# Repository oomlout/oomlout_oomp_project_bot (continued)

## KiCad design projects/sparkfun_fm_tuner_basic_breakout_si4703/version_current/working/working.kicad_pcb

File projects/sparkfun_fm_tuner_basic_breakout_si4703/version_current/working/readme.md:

# FM_Tuner_Basic_Breakout-Si4703 by sparkfun  
This is a harvested standardized copy of a project from github.  
The original project can be found at:  
https://github.com/sparkfun/FM_Tuner_Basic_Breakout-Si4703  
Please consult that link for additional, details, files, and license information.  
Note: It was auto harvested and if the original repo had more than one board file or anything out of the ordinary the files here are likely not representative.

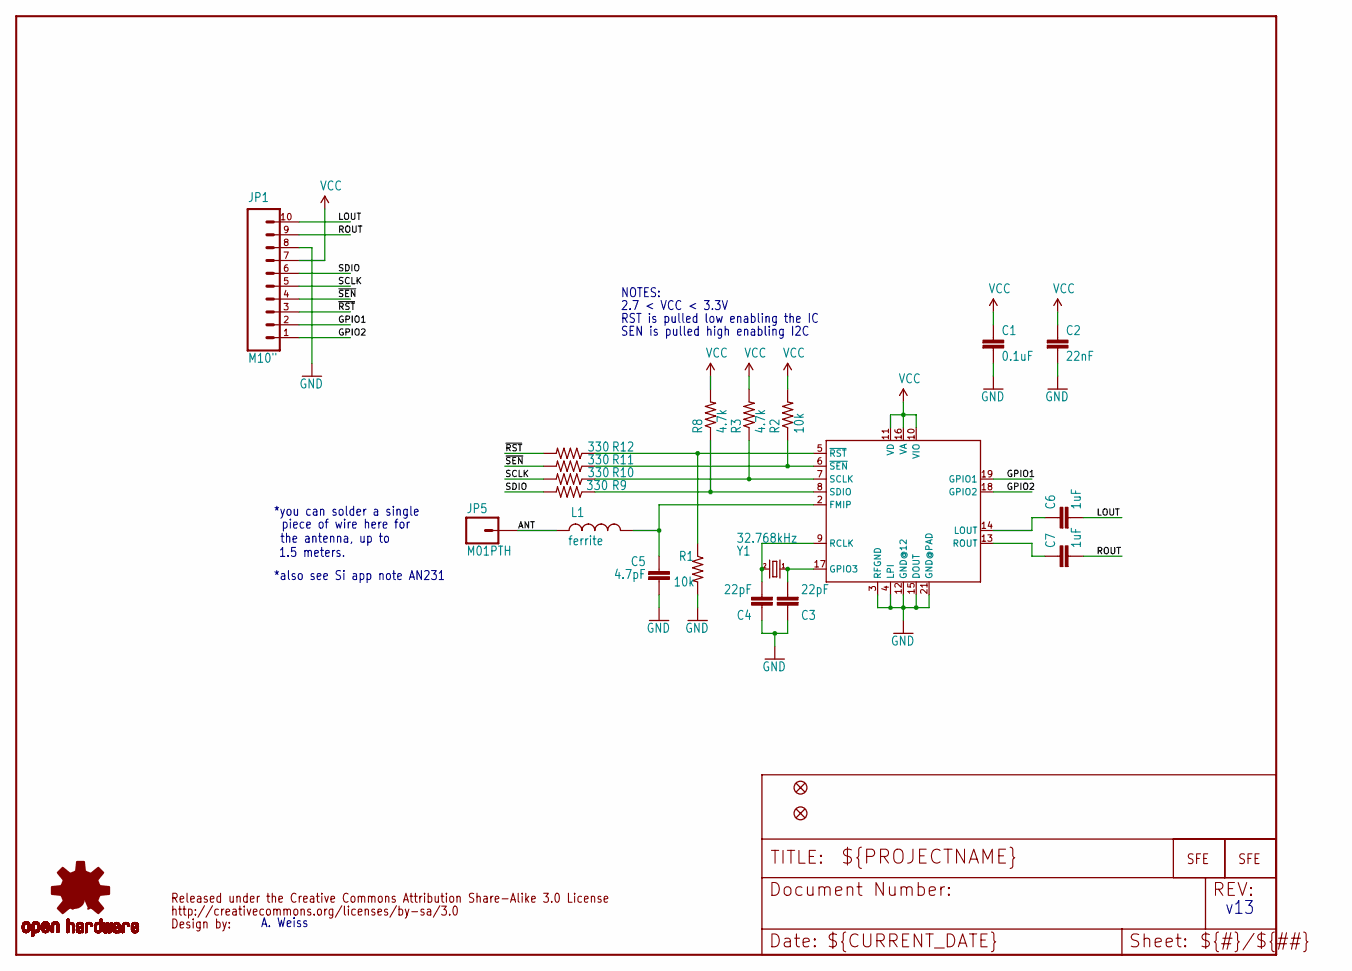
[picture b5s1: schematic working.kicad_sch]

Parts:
C1: 0.1uF; 0402-CAP
C2: 22nF; 0402-CAP
C3, C4: 22pF; 0402-CAP
C5: 4.7pF; 0402-CAP
C6, C7: 1uF; 0402-CAP
JP1: M10"; 1X10
JP2: LOGO-SFENW2; SFE-NEW-WEB
JP3: LOGO-SFESK; SFE-LOGO-FLAME
JP4, JP6: FIDUCIALUFIDUCIAL; MICRO-FIDUCIAL
JP5: M01PTH; 1X01
L1: ferrite; C0402
R1, R2: 10k; 0402-RES
R3, R8: 4.7k; 0402-RES
R9, R10, R11, R12: 330; 0402-RES
U1: SPARKFUN_SI470X
U$1: CREATIVE_COMMONS
U$3: OSHW-LOGOS; OSHW-LOGO-S
Y1: 32.768kHz; CRYSTAL-32KHZ-SMD

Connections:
3.3V: C1.1, C2.1, JP1.7, R2.2, R3.2, R8.2, U1.10 (VIO), U1.11 (VD), U1.16 (VA)
ANT: JP5.1, L1.1
GND: C1.2, C2.2, C3.1, C4.1, C5.2, JP1.8, R1.2, U1.3 (RFGND), U1.4 (LPI), U1.12 (GND@12), U1.15 (DOUT), U1.21 (GND@PAD)
GPIO1: JP1.2, U1.19 (GPIO1)
GPIO2: JP1.1, U1.18 (GPIO2)
LOUT: C6.2, JP1.10
unnamed: C4.2, U1.9 (RCLK), Y1.X2 (2)
unnamed: C3.2, U1.17 (GPIO3), Y1.X1 (1)
unnamed: C5.1, L1.2, U1.2 (FMIP)
unnamed: C6.1, U1.14 (LOUT)
unnamed: C7.1, U1.13 (ROUT)
ROUT: C7.2, JP1.9
SCLK: JP1.5, R10.2
SCLK-L: R3.1, R10.1, U1.7 (SCLK)
SDIO: JP1.6, R9.2
SDIO-L: R8.1, R9.1, U1.8 (SDIO)
~RST-L: R1.1, R12.1, U1.5 (~RST)
~RST: JP1.3, R12.2
~SEN-L: R2.1, R11.1, U1.6 (~SEN)
~SEN: JP1.4, R11.2

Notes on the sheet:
*also see Si app note AN231
SEN is pulled high enabling I2C
*you can solder a single
v13
A. Weiss
piece of wire here for
NOTES:
1.5 meters.
RST is pulled low enabling the IC
2.7 < VCC < 3.3V
the antenna, up to

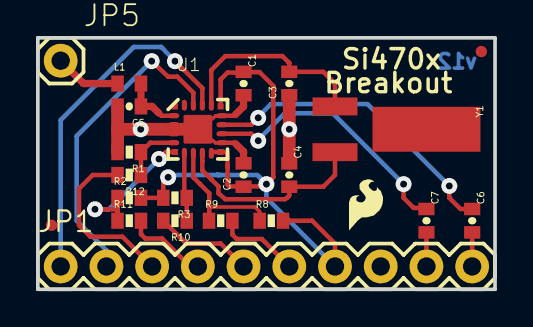
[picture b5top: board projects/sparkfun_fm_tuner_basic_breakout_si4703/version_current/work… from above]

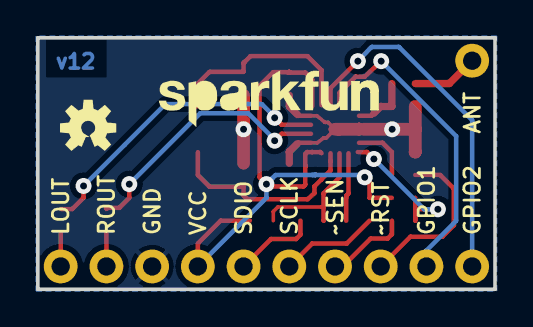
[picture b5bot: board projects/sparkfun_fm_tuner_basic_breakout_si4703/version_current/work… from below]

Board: 2 copper layers, 25.4 x 14.0 mm, 26 parts (2 on the bottom side), 20 nets.

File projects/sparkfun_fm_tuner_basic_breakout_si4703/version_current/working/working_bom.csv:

Row,Description,Part,References,Value,Footprint,Quantity Per PCB,Status,Datasheet,RESISTANCE
1,,CAP0402-CAP,C5,4.7pF,0402-CAP,1, ,,
2,,CAP0402-CAP,C3 C4,22pF,0402-CAP,2, ,,
3,,CAP0402-CAP,C2,22nF,0402-CAP,1, ,,
4,,CAP0402-CAP,C1,0.1uF,0402-CAP,1, ,,
5,,CAP0402-CAP,C6 C7,1uF,0402-CAP,2, ,,
6,,LOGO-SFENW2,JP2,LOGO-SFENW2,SFE-NEW-WEB,1, ,,
7,,LOGO-SFESK,JP3,LOGO-SFESK,SFE-LOGO-FLAME,1, ,,
8,,M01PTH,JP5,M01PTH,1X01,1, ,,
9,,M10{dblquote},JP1,M10{dblquote},1X10,1, ,,
10,,INDUCTOR0402,L1,ferrite,C0402,1, ,,75 Ohm
11,,RESISTOR0402-RES,R9 R10 R11 R12,330,0402-RES,4, ,,
12,,RESISTOR0402-RES,R3 R8,4.7k,0402-RES,2, ,,
13,,RESISTOR0402-RES,R1 R2,10k,0402-RES,2, ,,
14,,SPARKFUN_SI470X,U1,SPARKFUN_SI470X,SPARKFUN_SI470X,1, ,,
15,,CREATIVE_COMMONS,U$1,CREATIVE_COMMONS,CREATIVE_COMMONS,1, ,,
16,,OSHW-LOGOS,U$3,OSHW-LOGOS,OSHW-LOGO-S,1, ,,
17,,CRYSTAL32-SMD,Y1,32.768kHz,CRYSTAL-32KHZ-SMD,1, ,,





Project info:
Schematic:,working
Variant:,default
Revision:,
Date:,2023-08-06_12-56-02
KiCad Version:,7.0.6-7.0.6~ubuntu22.04.1
Statistics:
Component Groups:,17
Component Count:,24 (0 SMD/ 0 THT)
Fitted Components:,24 (0 SMD/ 0 THT)
Number of PCBs:,1
Total Components:,24

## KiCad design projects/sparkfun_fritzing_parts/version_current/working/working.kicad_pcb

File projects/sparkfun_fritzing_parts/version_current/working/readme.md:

# OOMP Project  
## Fritzing_Parts  by sparkfun  
  
oomp key: oomp_projects_flat_sparkfun_fritzing_parts  
(snippet of original readme)  
  
Fritzing Parts  
==============  
  
This repo houses all of the SFE Fritzing parts for use in diagrams in tutorials. If you create a new part in Fritzing that correlates to an SFE part, please add it here so others may use it and to avoid duplication. Make sure to also check Fritzing software for additional boards.   
  
Repository Contents  
-------------------  
  
* **/kits** - Fritzing circuits (**&-42;.fzz**) and images (**&-42;.png**)from a few of our Inventor's Kits  
* **/parts** - Common Fritzing parts and vector (**&-42;.svg**) files of individual components on SparkFun boards  
* **/products** - Fritzing boards (**&-42;.fzpz** and some **&-42;.fzz**)  
* **/templates** - SparkFun T5403 Barometer Breakout vector (**&-42;.svg**) templates used in the SparkFun tutorial to [Make Your Own Fritzing Part]((https://learn.sparkfun.com/tutorials/make-your-own-fritzing-parts) )  
  
Documentation  
-------------  
* [Make Your Own Fritzing Parts](https://learn.sparkfun.com/tutorials/make-your-own-fritzing-parts)   
  
Contributing/Adding Fritzing Parts  
---------------------------------  
  
Please check out the Fritzing tutorial [here](https://github.com/fritzing/fritzing-parts/blob/master/CONTRIBUTING.md) for more information.   
  
  full source readme at [readme_src.md](readme_src.md)  
  
source repo at: [https://github.com/sparkfun/Fritzing_Parts](https://github.com/sparkfun/Fritzing_Parts)  
## Board  

## Schematic  

[schematic pdf](working_schematic.pdf)  
## Images

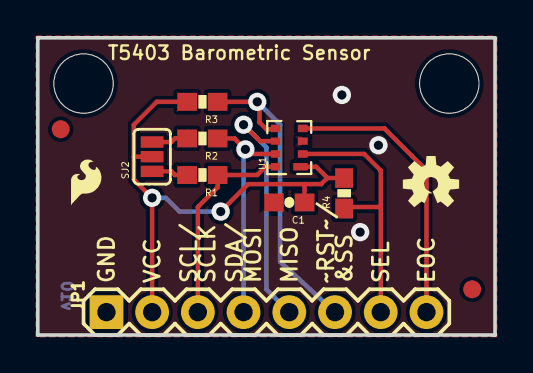
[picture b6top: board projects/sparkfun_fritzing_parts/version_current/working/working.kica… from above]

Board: 2 copper layers, 25.4 x 16.5 mm, 16 parts (1 on the bottom side), 10 nets.

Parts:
C1: .1uF; 0603-CAP
FID1, FID2: FIDUCIAL1X2; FIDUCIAL-1X2
FRAME1: FRAME-LETTER; CREATIVE_COMMONS
JP1: 1X08
LOGO1: LOGO-SFENEW; SFE-NEW-WEBLOGO
LOGO2: OSHW-LOGOS; OSHW-LOGO-S
LOGO3: SFE_LOGO_FLAME.1_INCH; SFE_LOGO_FLAME_.1
R1, R2: 4.7k; 0603-RES
R3, R4: 10k; 0603-RES
SJ2: SJ_3_PASTE1&2&3
STANDOFF1, STANDOFF2: STAND-OFF
U1: T5400

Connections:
EOC: JP1.8, U1.4
GND: C1.2, JP1.1, U1.3
MISO: JP1.5, U1.6
unnamed: R2.2, SJ2.3
unnamed: R1.2, SJ2.1
SCL/SCLK: JP1.3, R1.1, U1.8
SDA/MOSI: JP1.4, R2.1, U1.7
SEL: JP1.7, R4.1, U1.2
VCC: C1.1, JP1.2, R3.2, R4.2, SJ2.2, U1.1
~RST/&SS: JP1.6, R3.1, U1.5

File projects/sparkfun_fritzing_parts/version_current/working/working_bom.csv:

"Id";"Designator";"Footprint";"Quantity";"Designation";"Supplier and ref";
1;"LOGO2";"OSHW-LOGO-S";1;"OSHW-LOGOS";;;
2;"STANDOFF1,STANDOFF2";"STAND-OFF";2;"STAND-OFF";;;
3;"R2,R1";"0603-RES";2;"4.7k";;;
4;"FRAME1";"CREATIVE_COMMONS";1;"FRAME-LETTER";;;
5;"SJ2";"SJ_3_PASTE1&2&3";1;"";;;
6;"LOGO3";"SFE_LOGO_FLAME_.1";1;"SFE_LOGO_FLAME.1_INCH";;;
7;"R3,R4";"0603-RES";2;"10k";;;
8;"FID1,FID2";"FIDUCIAL-1X2";2;"FIDUCIAL1X2";;;
9;"JP1";"1X08";1;"";;;
10;"C1";"0603-CAP";1;".1uF";;;
11;"U1";"T5400";1;"T5400";;;
12;"LOGO1";"SFE-NEW-WEBLOGO";1;"LOGO-SFENEW";;;

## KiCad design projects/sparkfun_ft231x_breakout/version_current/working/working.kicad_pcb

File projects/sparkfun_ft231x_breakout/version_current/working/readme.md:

# OOMP Project  
## FT231X_Breakout  by sparkfun  
  
oomp key: oomp_projects_flat_sparkfun_ft231x_breakout  
(snippet of original readme)  
  
FT231X Breakout  
========================  
  
[    
*FT231X Breakout (BOB-11736)*](https://www.sparkfun.com/products/11736)  
  
This is a simple breakout board for the FTDI FT231X. A **USB to serial UART** interface with full modem control. The board has a micro USB connector, and other support circuitry to get the IC quickly up-and-running.  
  
Repository Contents  
-------------------  
  
* **/hardware** - PCB design files (created with Eagle 6.1.0)  
* **/Production Files** - Test bed files and production panel files  
  
License Information  
-------------------  
  
All contents of this repository are released under [Creative Commons Share-alike 3.0](http://creativecommons.org/licenses/by-sa/3.0/).  
  
Author  
------  
  
Jim Lindblom, [SparkFun Electronics](https://www.sparkfun.com)  
  
  full source readme at [readme_src.md](readme_src.md)  
  
source repo at: [https://github.com/sparkfun/FT231X_Breakout](https://github.com/sparkfun/FT231X_Breakout)  
## Board  

## Schematic  

[schematic pdf](working_schematic.pdf)  
## Images

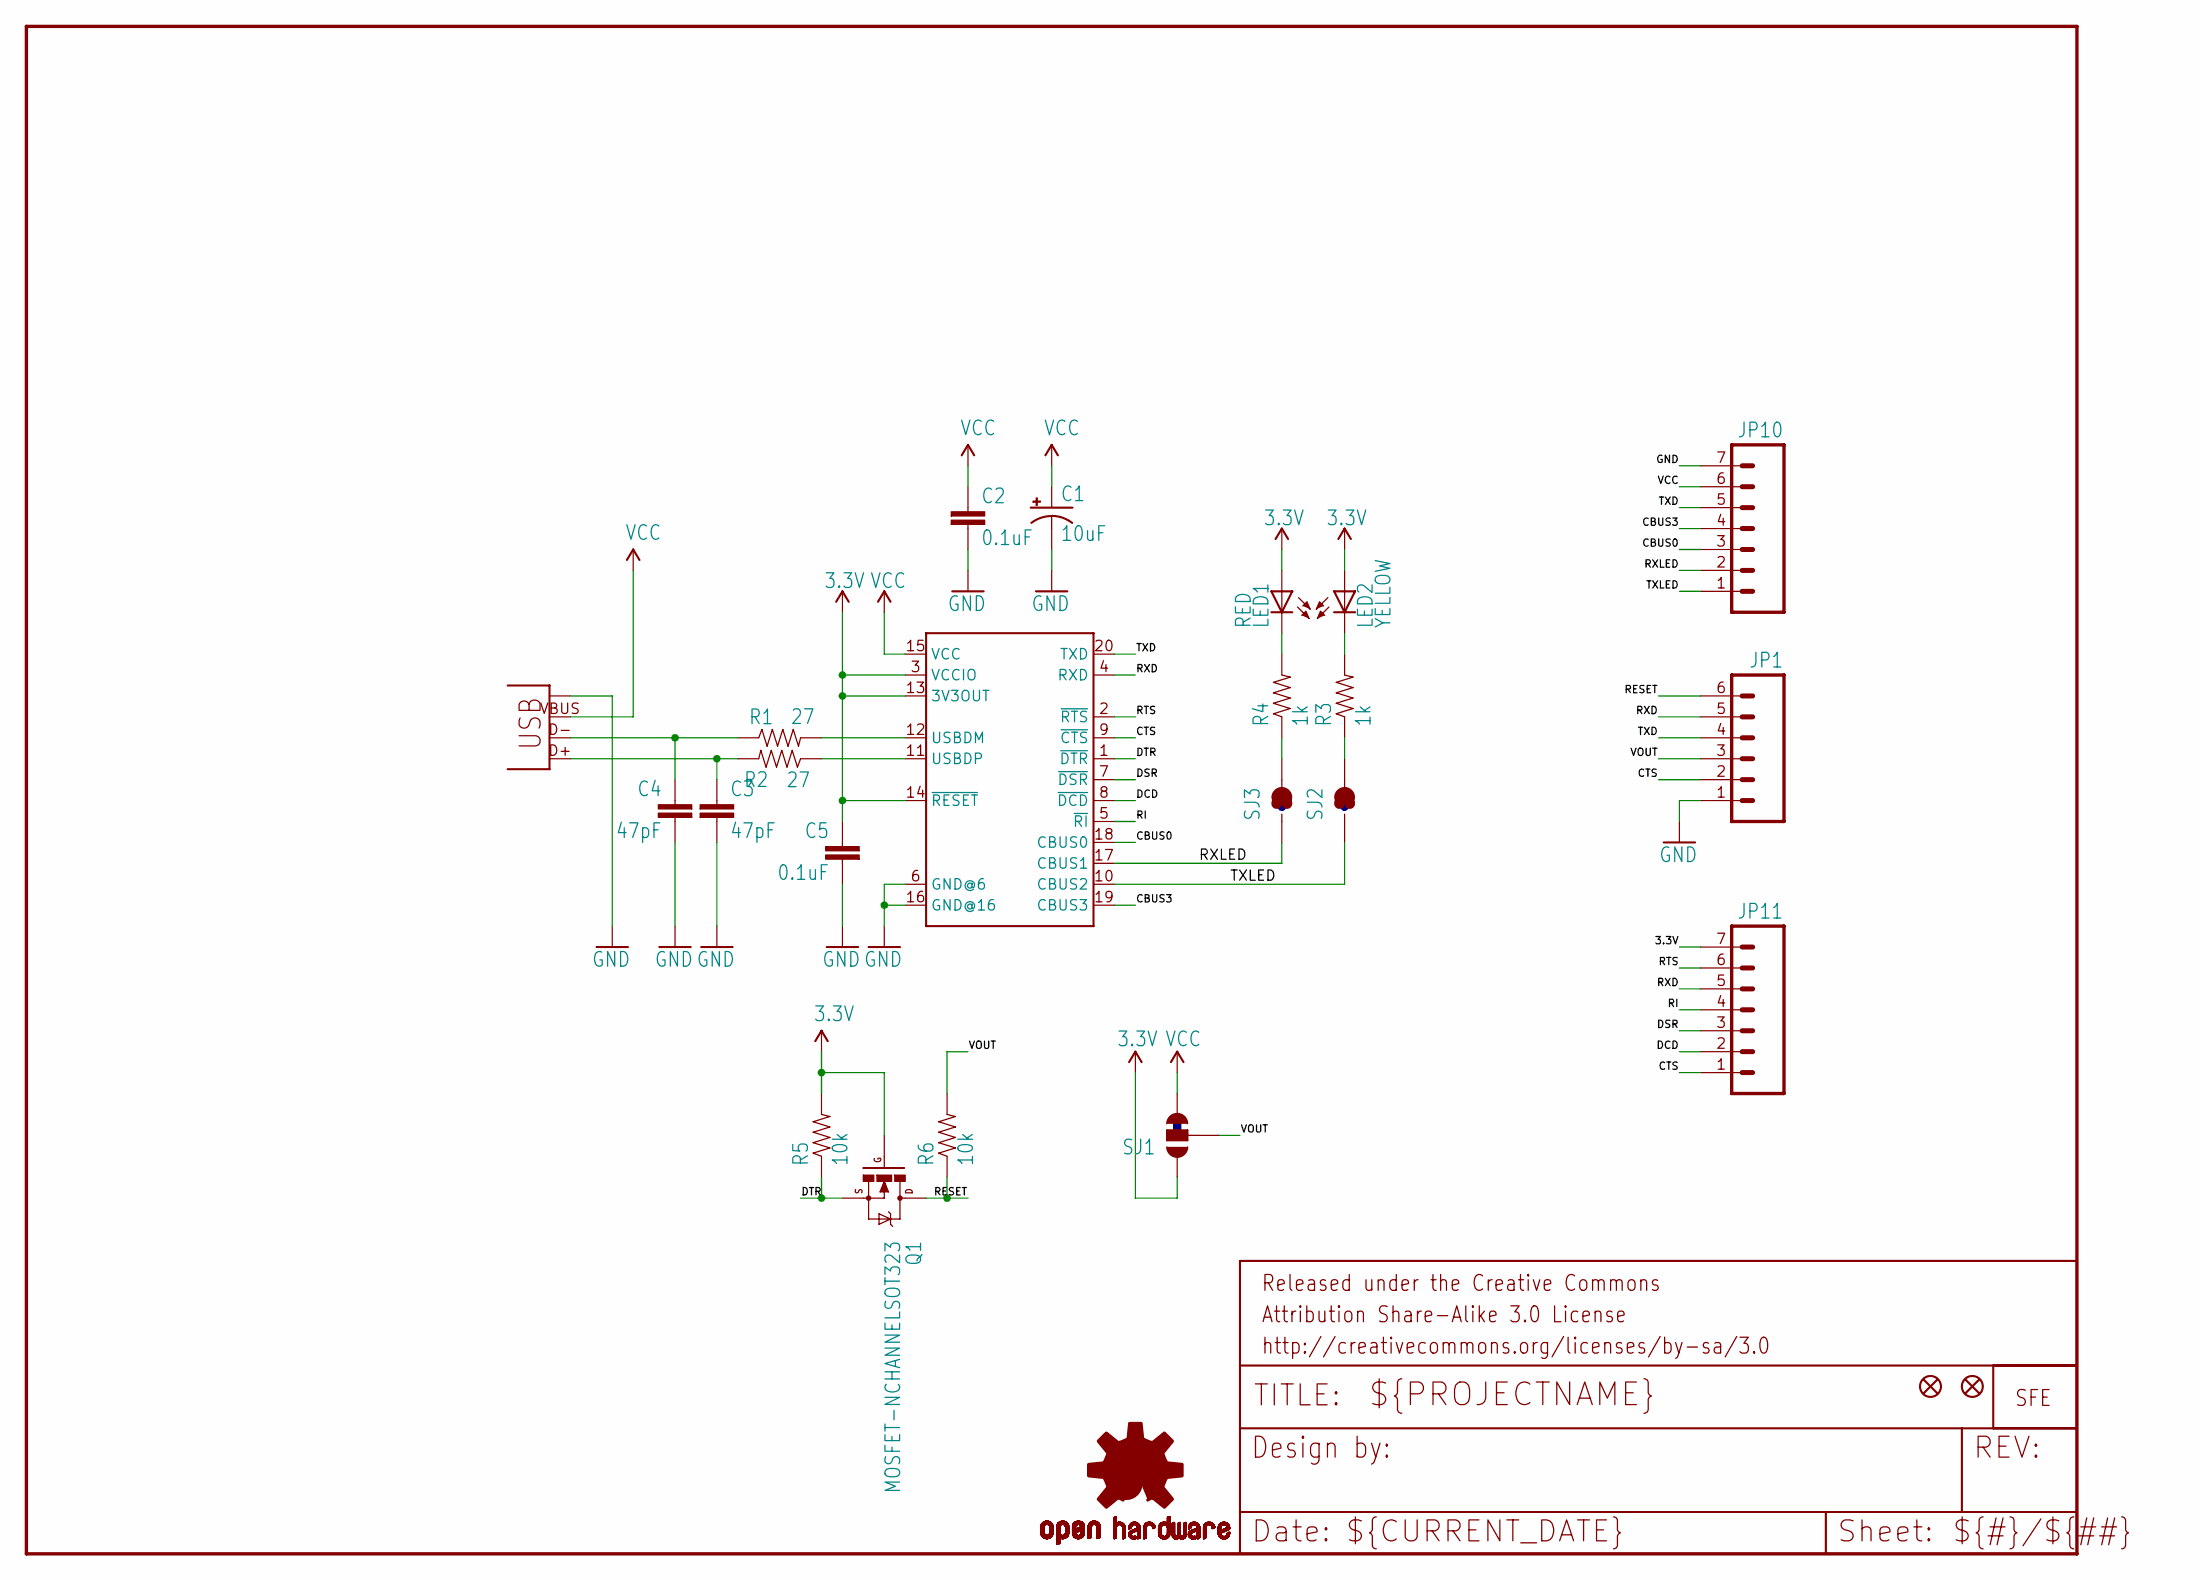
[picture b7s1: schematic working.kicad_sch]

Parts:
C1: 10uF; EIA3216
C2, C5: 0.1uF; 0402-CAP
C3, C4: 47pF; 0402-CAP
FRAME1: FRAME-LETTER; CREATIVE_COMMONS
JP1: M06SIP-NS; 1X06_NS
JP2: LOGO-SFENW2; SFE-NEW-WEB
JP3, JP4: FIDUCIALUFIDUCIAL; MICRO-FIDUCIAL
JP10, JP11: M07NS; 1X07_NS
LED1: RED; LED-0603
LED2: YELLOW; LED-0603
Q1: MOSFET-NCHANNELSOT323; SOT323
R1, R2: 27; 0402-RES
R3, R4: 1k; 0402-RES
R5, R6: 10k; 0402-RES
SJ1: SOLDERJUMPER_2WAYS; SJ_3
SJ2, SJ3: SOLDERJUMPERTRACE; SJ_2S-TRACE
U1: FT231XS; SSOP20_L
U$1: OSHW-LOGOS; OSHW-LOGO-S
X1: USB-MICROB

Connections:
3.3V: C5.1, JP11.7, LED1.A, LED2.A, Q1.1 (G), R5.2, SJ1.1, U1.3 (VCCIO), U1.13 (3V3OUT), U1.14 (~RESET)
CBUS0: JP10.3, U1.18 (CBUS0)
CBUS3: JP10.4, U1.19 (CBUS3)
CTS: JP1.2, JP11.1, U1.9 (~CTS)
DCD: JP11.2, U1.8 (~DCD)
DSR: JP11.3, U1.7 (~DSR)
DTR: Q1.2 (S), R5.1, U1.1 (~DTR)
GND: C1.C (-), C2.2, C3.2, C4.2, C5.2, JP1.1, JP10.7, U1.6 (GND@6), U1.16 (GND@16), X1.GND, X1.MT1 (GND), X1.MT2 (GND)
unnamed: R1.2, U1.12 (USBDM)
unnamed: R2.1, U1.11 (USBDP)
unnamed: C3.1, R2.2, X1.D+
unnamed: C4.1, R1.1, X1.D-
unnamed: LED2.C, R3.2
unnamed: LED1.C, R4.2
unnamed: R3.1, SJ2.2
unnamed: R4.1, SJ3.2
RESET: JP1.6, Q1.3 (D), R6.1
RI: JP11.4, U1.5 (~RI)
RTS: JP11.6, U1.2 (~RTS)
RXD: JP1.5, JP11.5, U1.4 (RXD)
RXLED: JP10.2, SJ3.1, U1.17 (CBUS1)
TXD: JP1.4, JP10.5, U1.20 (TXD)
TXLED: JP10.1, SJ2.1, U1.10 (CBUS2)
VCC: C1.A (+), C2.1, JP10.6, SJ1.3, U1.15 (VCC), X1.VBUS
VOUT: JP1.3, R6.2, SJ1.2

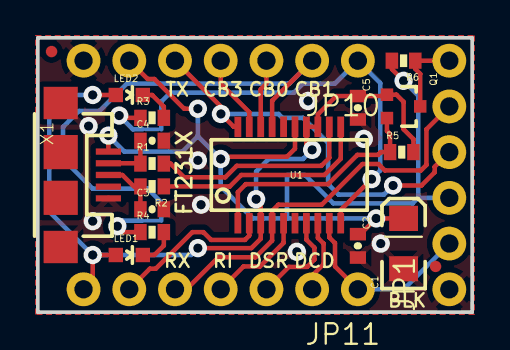
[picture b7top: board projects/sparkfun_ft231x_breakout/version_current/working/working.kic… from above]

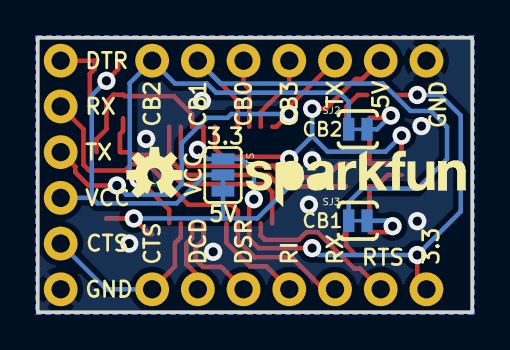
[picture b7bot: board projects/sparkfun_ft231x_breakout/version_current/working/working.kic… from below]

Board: 2 copper layers, 24.1 x 15.2 mm, 27 parts (5 on the bottom side), 25 nets.

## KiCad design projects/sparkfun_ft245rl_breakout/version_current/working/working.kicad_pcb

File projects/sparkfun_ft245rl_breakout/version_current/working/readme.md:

# OOMP Project  
## FT245RL_Breakout  by sparkfun  
  
oomp key: oomp_projects_flat_sparkfun_ft245rl_breakout  
(snippet of original readme)  
  
SparkFun USB to FIFO- FT245RL Breakout  
========================================  

[*SparkFun USB to FIFO- FT245RL Breakout (BOB-07841)*](https://www.sparkfun.com/products/7841)  
  
Basic breakout board for FTDI’s popular USB to FIFO IC.   
  
Repository Contents  
-------------------  
* **/Hardware** - All Eagle design files (.brd, .sch, .STL)  

License Information  
-------------------  
The hardware is released under [Creative Commons ShareAlike 4.0 International](https://creativecommons.org/licenses/by-sa/4.0/).  
  
Distributed as-is; no warranty is given.  
  
  full source readme at [readme_src.md](readme_src.md)  
  
source repo at: [https://github.com/sparkfun/FT245RL_Breakout](https://github.com/sparkfun/FT245RL_Breakout)  
## Board  

## Schematic  

[schematic pdf](working_schematic.pdf)  
## Images

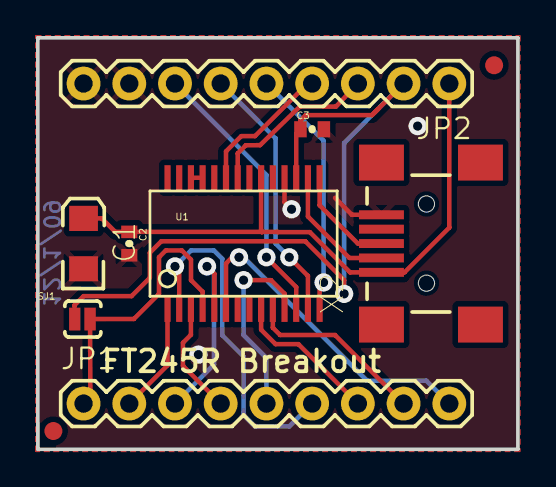
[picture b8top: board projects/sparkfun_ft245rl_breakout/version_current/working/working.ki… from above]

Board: 2 copper layers, 26.7 x 22.9 mm, 11 parts (1 on the bottom side), 19 nets.

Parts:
C1: 10uF; CPOL_1206
C2, C3: 0.1uF; 0402-CAP
JP1, JP2: M09; 1X09
JP3, JP4: FIDUCIAL1X2; FIDUCIAL-1X2
SJ1: SOLDERJUMPERNC2; SJ_2S-NOTRACE
U1: FT245RL; SSOP28DB
U$1: LOGO-SFENEW; SFE-NEW-WEBLOGO
X2: USBSMD; USB-MINIB

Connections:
3.3V: C3.1, JP2.2, SJ1.1, U1.17
D0: JP1.2, U1.1
D1: JP1.3, U1.5
D2: JP1.4, U1.3
D3: JP1.5, U1.11
D4: JP1.6, U1.2
D5: JP1.7, U1.9
D6: JP1.8, U1.10
D7: JP1.9, U1.6
GND: C1.C, C2.2, C3.2, JP2.8, JP2.9, U1.7, U1.18, U1.21, U1.25, U1.26, X2.GND
PWEN: JP2.7, U1.12
RD: JP2.6, U1.13
RXF: JP2.4, U1.23
TXE: JP2.3, U1.22
USB_D+: U1.15, X2.D+
USB_D-: U1.16, X2.D-
VCCIO: JP1.1, SJ1.2, U1.4
VUSB: C1.A, C2.1, JP2.1, U1.20, X2.VBUS
WR: JP2.5, U1.14
